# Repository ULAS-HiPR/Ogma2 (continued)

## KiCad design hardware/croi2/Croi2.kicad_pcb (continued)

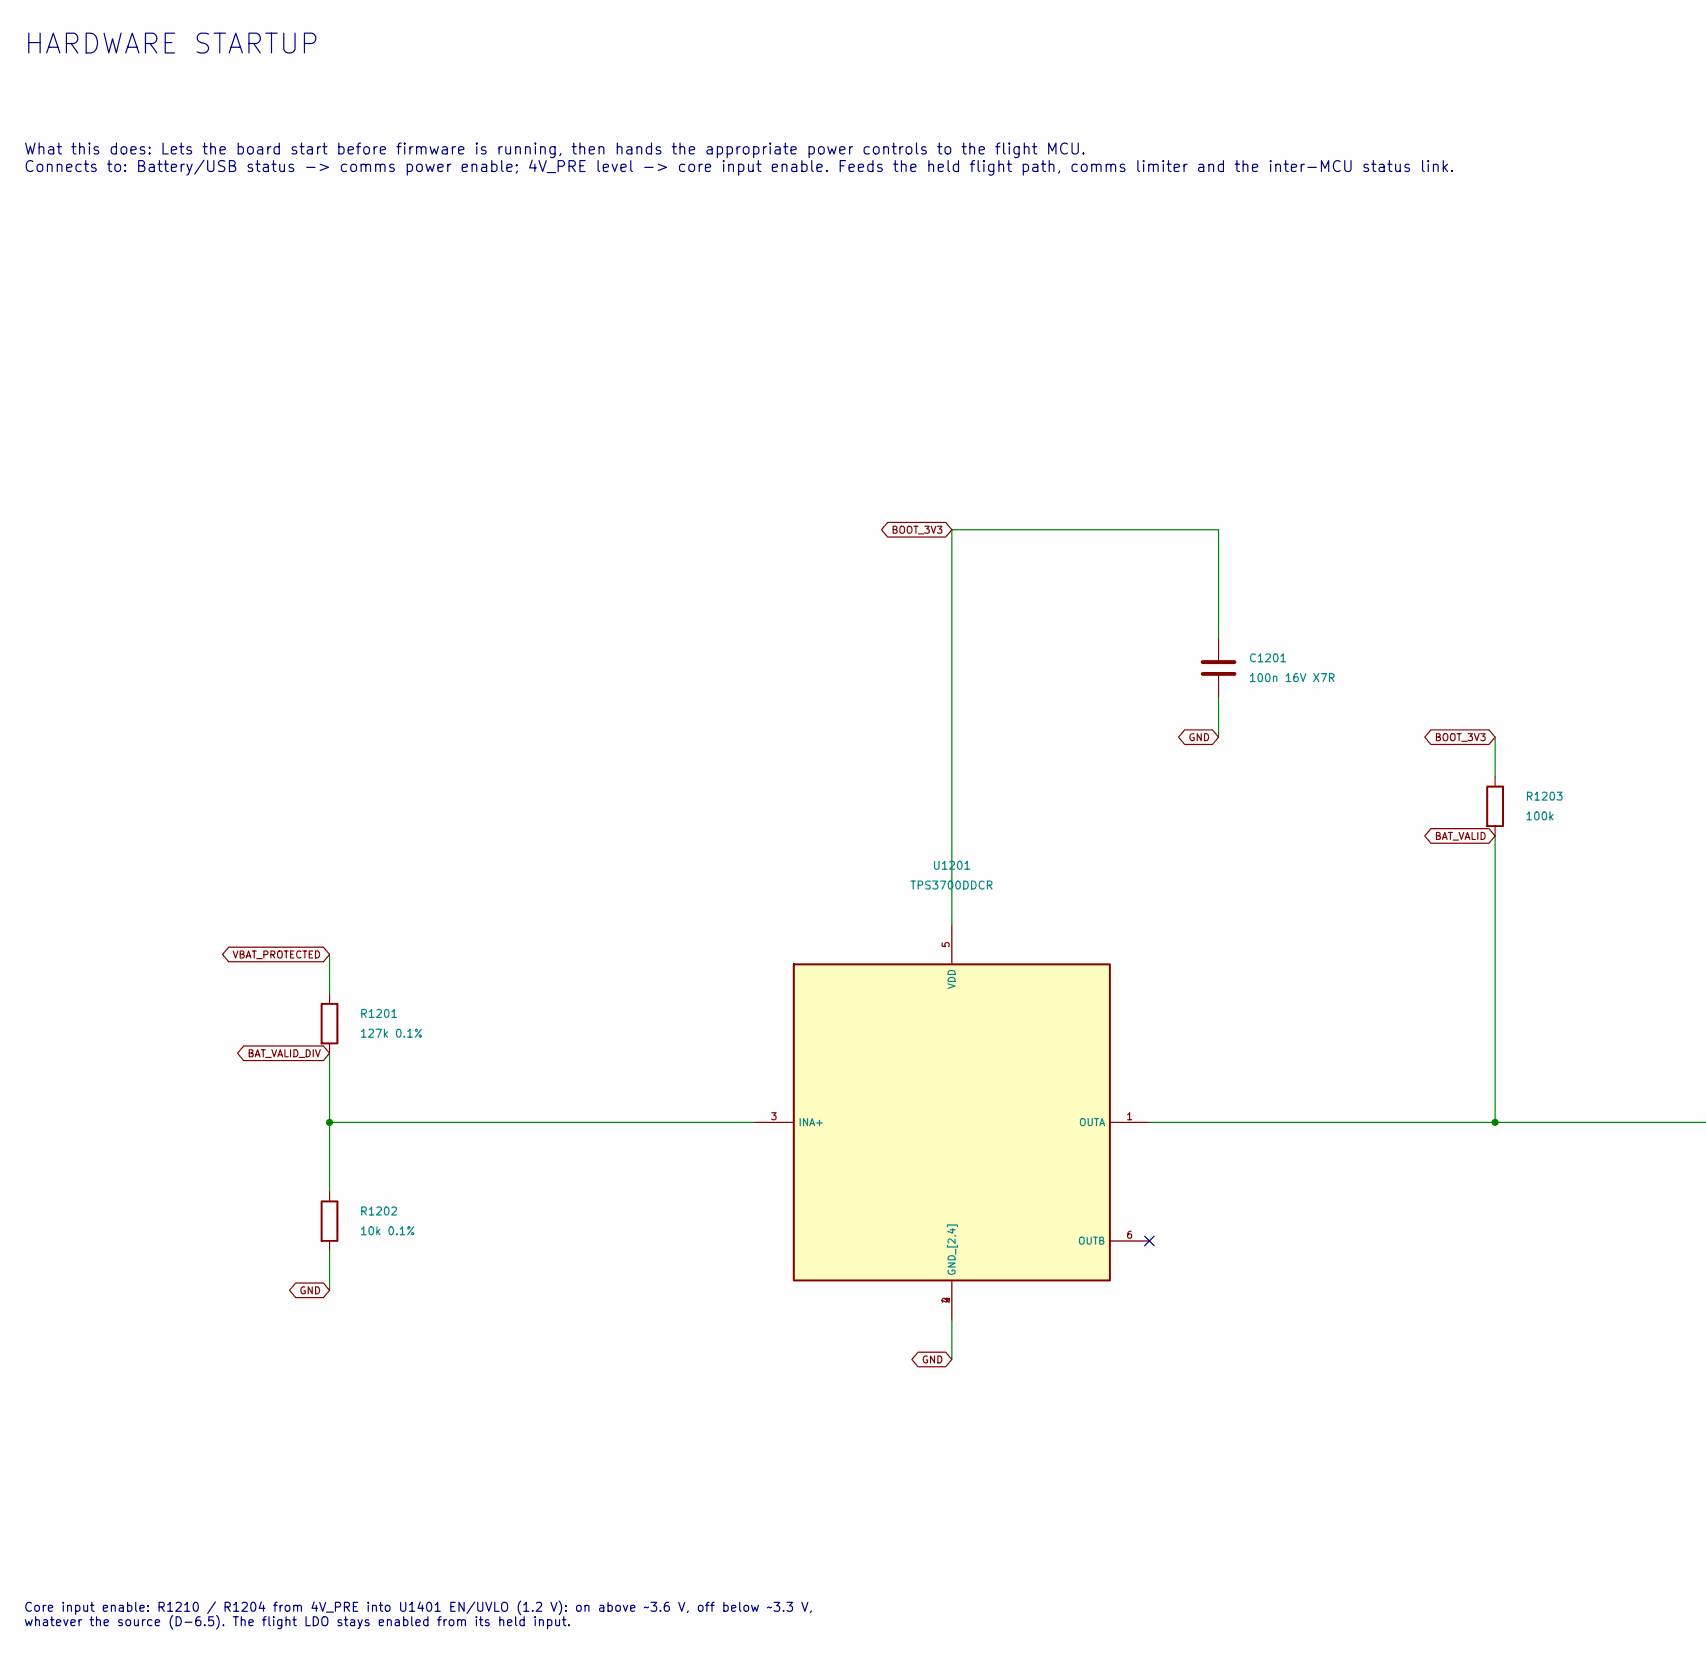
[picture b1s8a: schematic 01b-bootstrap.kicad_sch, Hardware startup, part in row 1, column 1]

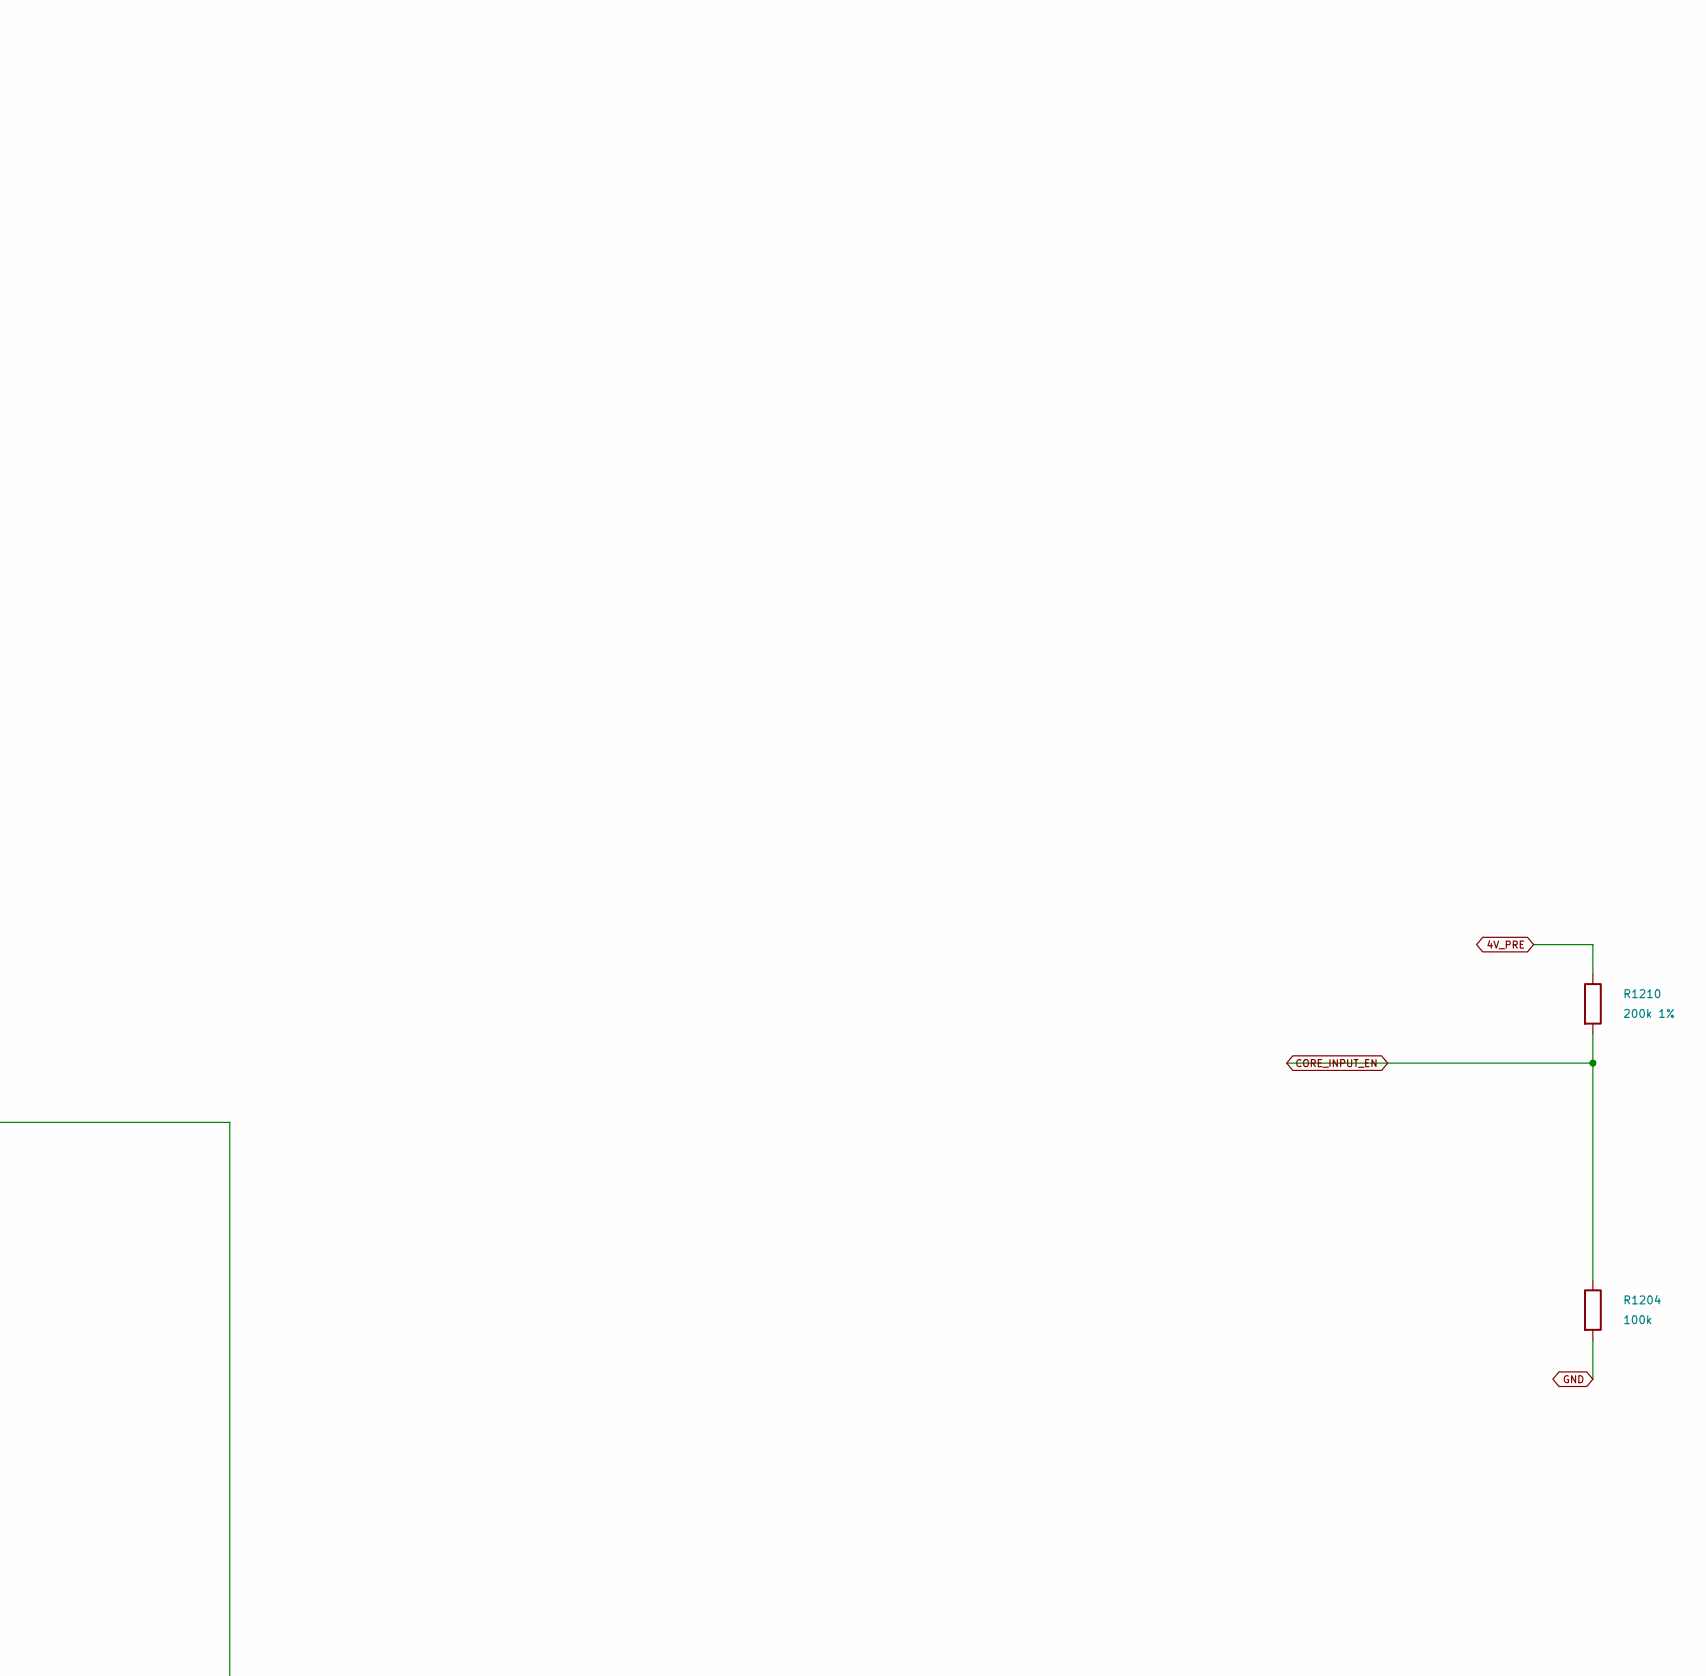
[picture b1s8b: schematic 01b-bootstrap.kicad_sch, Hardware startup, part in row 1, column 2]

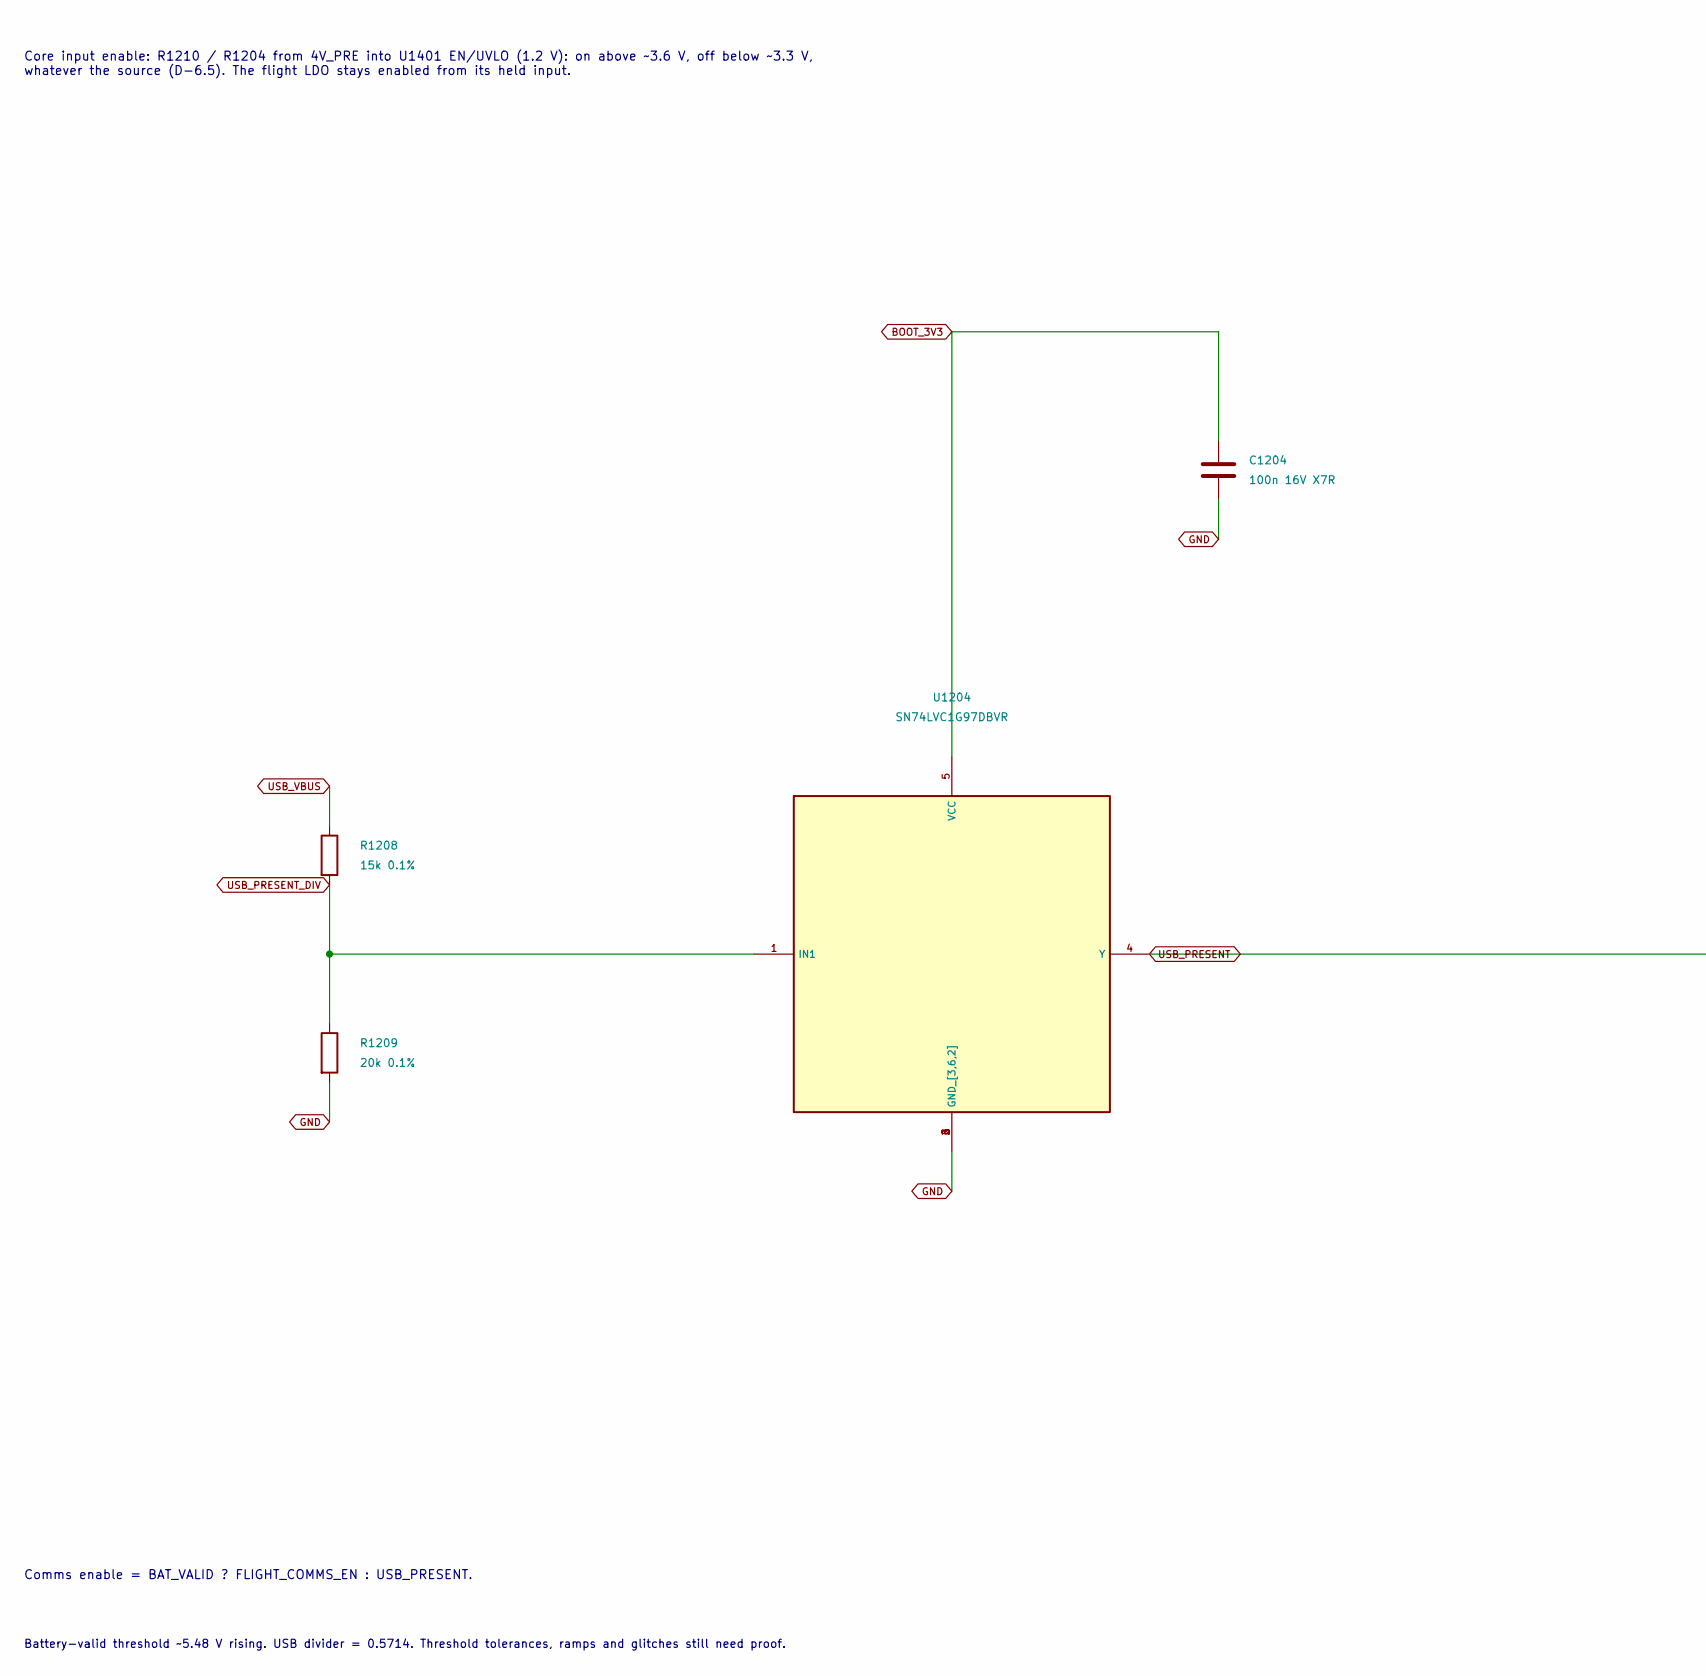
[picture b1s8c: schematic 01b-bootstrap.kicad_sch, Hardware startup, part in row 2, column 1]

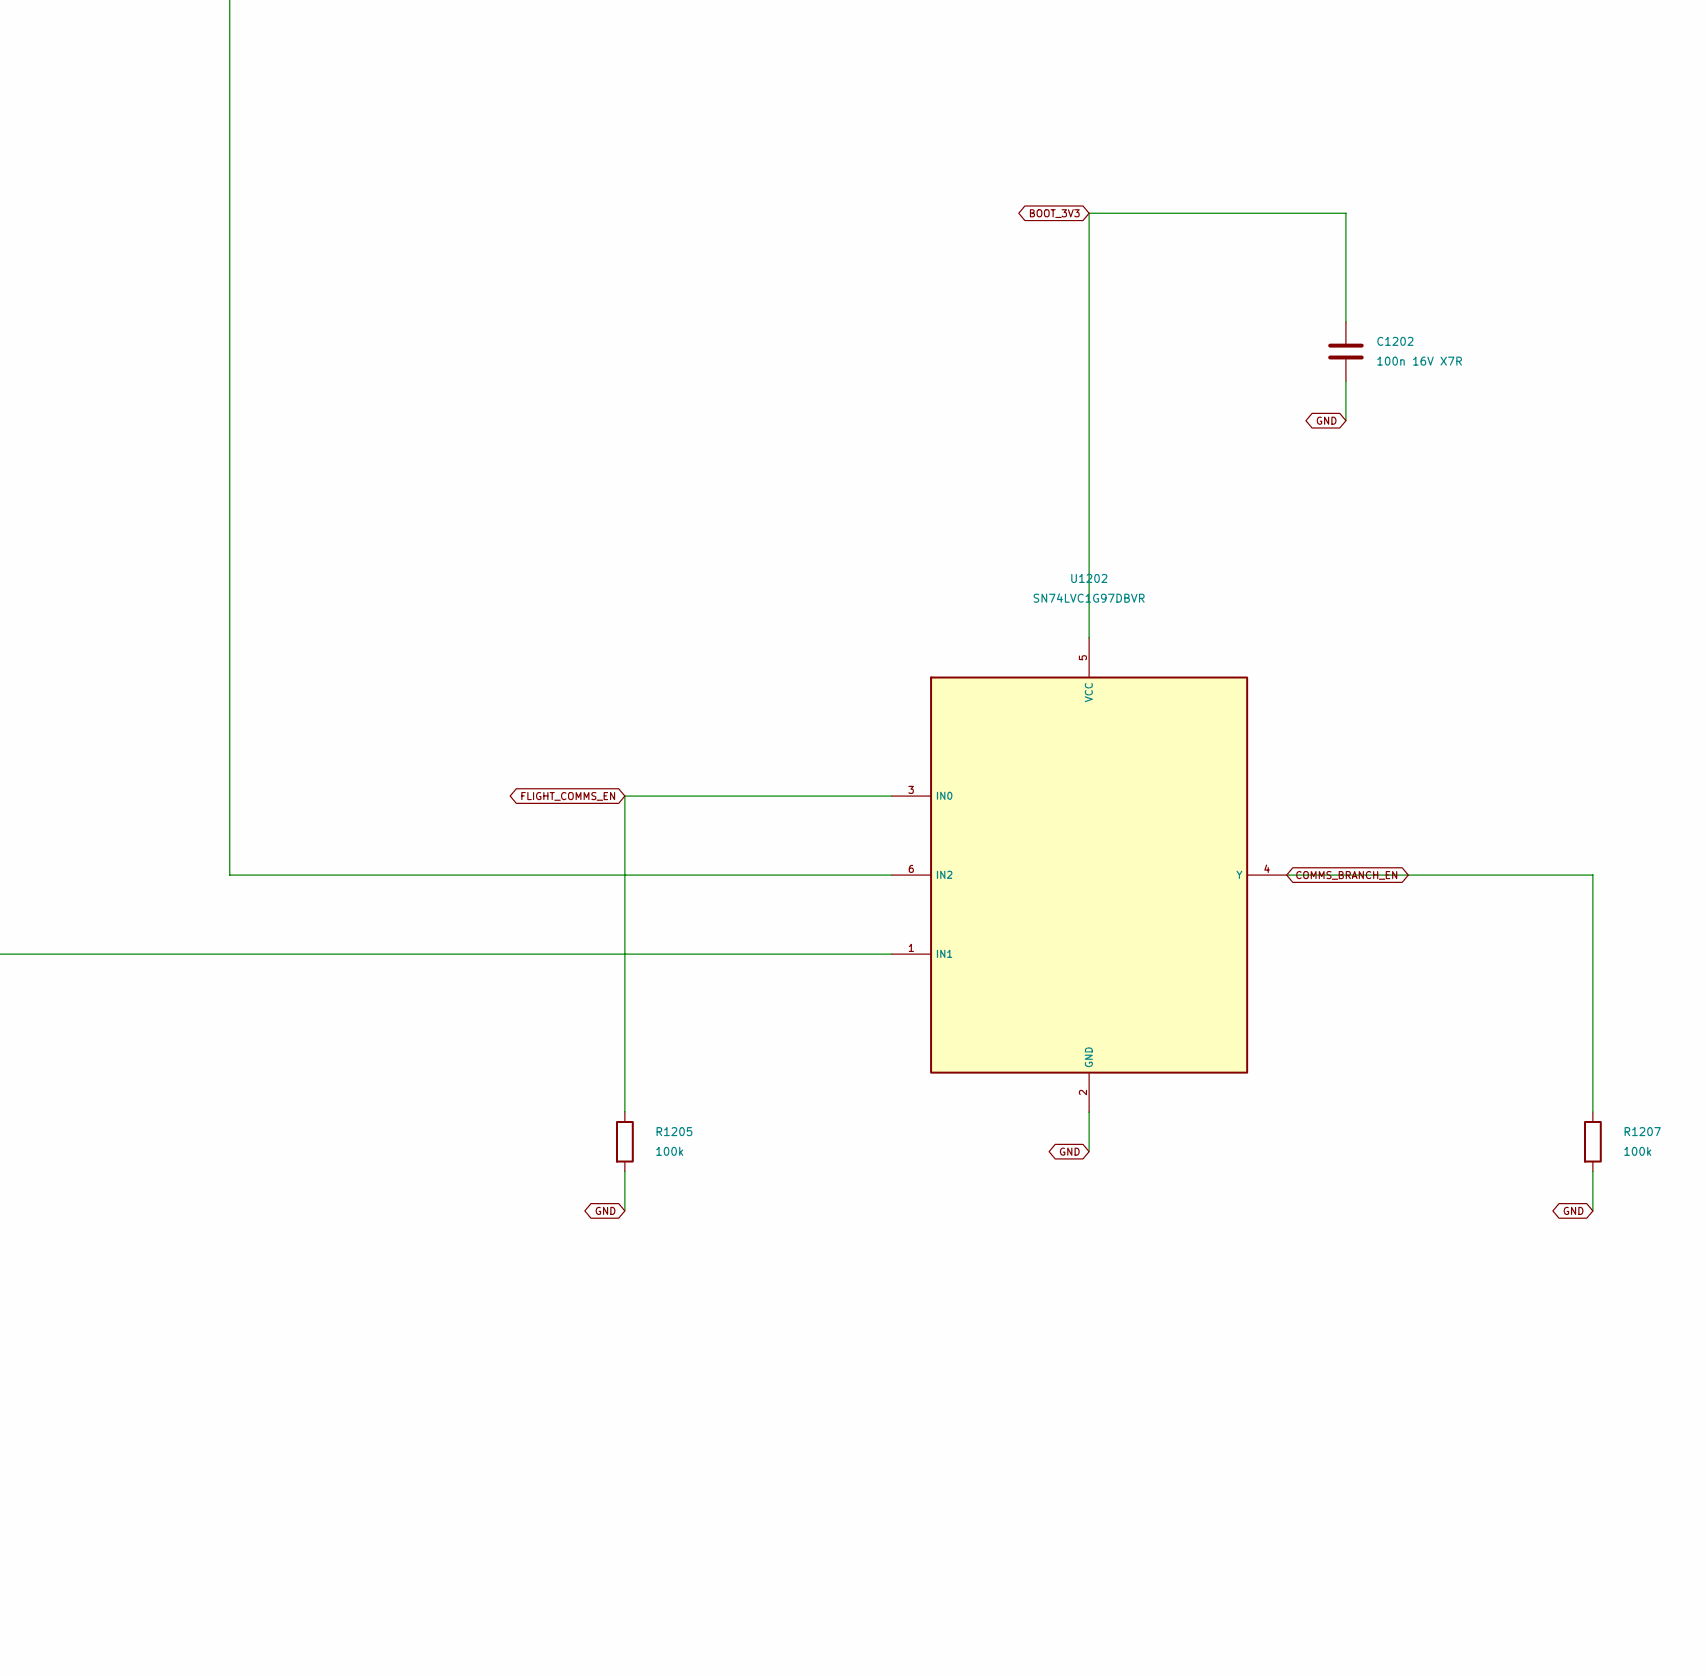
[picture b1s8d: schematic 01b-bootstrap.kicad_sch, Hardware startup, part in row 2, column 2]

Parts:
C1201, C1202, C1204: 100n 16V X7R; C_0402_1005Metric; MPN CL05B104KB54PNC; LCSC C307331
R1201: 127k 0.1%; R_0603_1608Metric
R1202: 10k 0.1%; R_0603_1608Metric
R1203, R1204, R1205, R1207: 100k; R_0402_1005Metric; MPN 0402WGF1003TCE; LCSC C25741
R1208: 15k 0.1%; R_0603_1608Metric
R1209: 20k 0.1%; R_0603_1608Metric
R1210: 200k 1%; R_0402_1005Metric; MPN 0402WGF2003TCE; LCSC C25764
U1201: TPS3700DDCR; MPN TPS3700DDCR
U1202, U1204: SN74LVC1G97DBVR; MPN SN74LVC1G97DBVR

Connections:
4V_PRE: R1210.1; also elsewhere on the board
BAT_VALID: R1203.2, U1201.1 (OUTA), U1202.6 (IN2); also elsewhere on the board
BAT_VALID_DIV: R1201.2, R1202.1, U1201.3 (INA+)
BOOT_3V3: C1201.1, C1202.1, C1204.1, R1203.1, U1201.5 (VDD), U1202.5 (VCC), U1204.5 (VCC); also elsewhere on the board
COMMS_BRANCH_EN: R1207.1, U1202.4 (Y); also elsewhere on the board
CORE_INPUT_EN: R1204.1, R1210.2; also elsewhere on the board
FLIGHT_COMMS_EN: R1205.1, U1202.3 (IN0); also elsewhere on the board
GND: C1201.2, C1202.2, C1204.2, R1202.2, R1204.2, R1205.2, R1207.2, R1209.2, U1201.2 (GND_[2,4]), U1201.4, U1202.2 (GND), U1204.2, U1204.3 (GND_[3,6,2]), U1204.6; also elsewhere on the board
USB_PRESENT: U1202.1 (IN1), U1204.4 (Y); also elsewhere on the board
USB_PRESENT_DIV: R1208.2, R1209.1, U1204.1 (IN1)
USB_VBUS: R1208.1; also elsewhere on the board
VBAT_PROTECTED: R1201.1; also elsewhere on the board

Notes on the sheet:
Core input enable: R1210 / R1204 from 4V_PRE into U1401 EN/UVLO (1.2 V): on above ~3.6 V, off below ~3.3 V, whatever the source (D-6.5). The flight LDO stays enabled from its held input.
Comms enable = BAT_VALID ? FLIGHT_COMMS_EN : USB_PRESENT.
Battery-valid threshold ~5.48 V rising. USB divider = 0.5714. Threshold tolerances, ramps and glitches still need proof.
HARDWARE STARTUP
What this does: Lets the board start before firmware is running, then hands the appropriate power controls to the flight MCU. Connects to: Battery/USB status -> comms power enable; 4V_PRE level -> core input enable. Feeds the held flight path, comms limiter and the inter-MCU status link.

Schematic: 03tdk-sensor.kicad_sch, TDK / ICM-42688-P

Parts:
C3202: 1u 16V X7R; C_0603_1608Metric
C3207: 100n 16V X7R; C_0402_1005Metric; MPN CL05B104KB54PNC; LCSC C307331
C3208: 2.2u 16V X7R; C_0603_1608Metric
C3209: 10n 16V X7R; C_0402_1005Metric; MPN CL05B103KB5NNNC; LCSC C15195
R3201: 47R 1%; R_0402_1005Metric; MPN RC0402FR-0747RL; LCSC C137973
R3205: 47k; R_0402_1005Metric; MPN 0402WGF4702TCE; LCSC C25792
R3207, R3208: 22R; R_0402_1005Metric; MPN 0402WGF220JTCE; LCSC C25092
U3204: ICM-42688-P; MPN ICM-42688-P

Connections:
FLIGHT_3V3: R3201.1, R3205.1; also elsewhere on the board
GND: C3202.2, C3207.2, C3208.2, C3209.2, U3204.6 (GND_[6,7]), U3204.7; also elsewhere on the board
TDK_3V3: C3202.1, C3207.1, C3208.1, C3209.1, R3201.2, U3204.5 (SUPPLY_[5,8]), U3204.8
TDK_DRDY: U3204.4 (INT1_INT); also elsewhere on the board
TDK_MISO: U3204.1 (AP_SDO_AD0); also elsewhere on the board
TDK_MOSI: R3208.1; also elsewhere on the board
TDK_MOSI_DAMP: R3208.2, U3204.14 (AP_SDA_SDIO_SDI)
TDK_NCS: R3205.2, U3204.12 (AP_CS); also elsewhere on the board
TDK_SCK: R3207.1; also elsewhere on the board
TDK_SCK_DAMP: R3207.2, U3204.13 (AP_SCL_SCLK)

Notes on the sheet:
2 FLIGHT-TO-SENSOR SPI
No switches or isolators (D-6.6). Firmware parks a dead sensor's bus pins so the MCU cannot back-power it through the 22 ohm damping (D-2Nov.3). Pull-ups go to FLIGHT_3V3.
1 SUPPLY LINK
What this does: Measures low-g acceleration and rotation with a second IMU from TDK. Connects to: Flight MCU SPI/control/interrupt pins -> this sensor. Fed from FLIGHT_3V3 through R3201, a 47 ohm link, like the ST IMU (D-6.6, D-2Nov.3).
TDK / ICM-42688-P

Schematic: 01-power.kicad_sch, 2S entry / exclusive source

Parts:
C1001: 22n 25V X7R; C_0603_1608Metric
C1002, C1003, C1004: 100n 50V X7R; C_0603_1608Metric
C1005: 10u 16V X7R; C_1206_3216Metric
C1007: 470u 6.3V Al; CP_Elec_6.3x7.7; MPN EEEFKJ471XSP
D1003, D1004: BAT54T1G; D_SOD-123; MPN BAT54T1G
J101: 1053111102; 105311-1102; MPN 1053111102
J102: BM06B-GHS-TBT; JST_GH_BM06B-GHS-TBT_1x06-1MP_P1.25mm_Vertical; MPN BM06B-GHS-TBT(LF)(SN)
Q101: CSD18540Q5B; MPN CSD18540Q5B
Q102: 2N7002; SOT-23
R1001: 100k 0.1%; R_0603_1608Metric
R1002: 22.1k 0.1%; R_0603_1608Metric
R1003: 64.9k 0.1%; R_0603_1608Metric
R1004, R1008: 10k 0.1%; R_0603_1608Metric
R1005: 3k 1%; R_0603_1608Metric
R1006: 22.1k 1%; R_0402_1005Metric; MPN RC0402FR-0722K1L; LCSC C163478
R1007: 39.2k 0.1%; R_0603_1608Metric
R1009: 10k; R_0603_1608Metric
R1010: 100k; R_0402_1005Metric; MPN 0402WGF1003TCE; LCSC C25741
R1011: 0R; R_0603_1608Metric
R1014: 330R; R_0603_1608Metric
R1015: 1M; R_0402_1005Metric; MPN 0402WGF1004TCE; LCSC C26083
TP41: BAT_SOURCE_PG; TestPoint_Pad_D1.0mm
TP42: VBAT_BURRITO_INPUT; TestPoint_Keystone_5190TR_ColorKeyed; MPN 5194TR; LCSC C22388408
TP43: BAT_BLOCK_GATE; TestPoint_Pad_D1.0mm
TP46: VBAT_PROTECTED; TestPoint_Keystone_5190TR_ColorKeyed; MPN 5194TR; LCSC C22388408
U101: TPS26630RGER; MPN TPS26630RGER

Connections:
/01-power/POWER_HOLD_RC: C1007.1, D1003.2 (A), D1004.2 (A), R1014.2
BAT_BLOCK_DRV: Q102.1 (G), U101.4 (DRV)
BAT_BLOCK_GATE: Q101.4 (G), Q102.3 (D), TP43.1 (1_1), U101.3 (B_GATE)
BAT_ILIM: R1005.1, U101.10 (ILIM)
BAT_IMON: R1009.1, U101.13 (IMON)
BAT_OV_DIV: R1003.2, R1004.1, U101.7 (OVP)
BAT_PG_DIV: R1007.2, R1008.1, U101.15 (PGTH)
BAT_SHDN_N: D1003.1 (K), R1006.1, U101.12 (~SHDN); also elsewhere on the board
BAT_SLEW: C1001.1, U101.9 (dVdT)
BAT_SOURCE_FAULT_N: R1011.1, U101.14 (~FLT); also elsewhere on the board
BAT_SOURCE_PG: R1010.2, TP41.1 (1_1), U101.16 (PGOOD)
BAT_UV_DIV: R1001.2, R1002.1, U101.6 (UVLO)
BOOT_3V3: R1010.1; also elsewhere on the board
BRANCH_FAULT_N: R1011.2; also elsewhere on the board
ENERGY_TAP: C1004.1, C1005.1, Q101.5 (D), U101.1 (IN_[1,2]), U101.2; also elsewhere on the board
EXT_3V3: J102.1; also elsewhere on the board
EXT_IO1: D1004.1 (K), J102.5
EXT_IO2: J102.6; also elsewhere on the board
EXT_SCL: J102.2; also elsewhere on the board
EXT_SDA: J102.3; also elsewhere on the board
FC_POWER_HOLD: R1014.1, R1015.1; also elsewhere on the board
GND: C1001.2, C1002.2, C1003.2, C1004.2, C1005.2, C1007.2, J101.2, J102.4, R1002.2, R1004.2, R1005.2, R1006.2, R1008.2, R1009.2, R1015.2, U101.8, U101.11 (MODE), U101.25 (GND_[25,8]); also elsewhere on the board
VBAT_BURRITO_INPUT: C1002.1, J101.1, Q101.1 (SUPPLY_[1,2,3]), Q101.2, Q101.3, Q102.2 (S), R1001.1, R1003.1, TP42.1 (1_1), U101.5 (IN_SYS); also elsewhere on the board
VBAT_PROTECTED: C1003.1, R1007.1, TP46.1 (1_1); also elsewhere on the board
VBAT_SHUNT_IN: U101.17 (SUPPLY_[17,18]), U101.18; also elsewhere on the board

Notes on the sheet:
UV / OV THRESHOLDS AND ENABLE DEFAULT
SOURCE ENTRY -> REVERSE BLOCKING -> ENERGY_TAP -> AUTO-RETRY EFUSE -> SHUNT ON BATTERY MONITOR SHEET
2S ENTRY / EXCLUSIVE SOURCE
ENABLE HOLD / FC_POWER_HOLD
Nano-Fit exact land pattern remains open. Samtec grounds are direct ground bonds. Only one battery source may be physically connected.
22.1k SHDN_N pull-down defaults the battery path OFF. The external master-enable circuit drives BAT_SHDN_N; it is not energetic isolation.
What this does: Accepts one 2S battery source, blocks reverse connection, shuts down a faulty input and retries, and holds the battery enable on through a flight-computer reset aloft (FC_POWER_HOLD). Connects to: Standalone battery or Churro mate -> battery monitor shunt -> logic and output branche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
COPLANAR CHURRO MATE / STANDALONE SOURCE EXCLUSION
Firmware drives PE5 high after launch detect; R1014 charges C1007 in about 0.5 s. If PE5 lets go (a reset aloft), C1007 keeps BAT_SHDN_N and, through J102.8, Churro's AV_SHDN_N above 2 V for >=0.75 s at the worst corner, against the ~0.6 s a restart and re-assert take (D-2Nov.4, D-2Nov.18). R1015 k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

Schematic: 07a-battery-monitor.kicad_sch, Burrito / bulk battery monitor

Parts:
C7101: 10n 100V C0G; C_0603_1608Metric
C7102: 10n 100V X7R; C_0603_1608Metric
C7103: 100n 16V X7R; C_0402_1005Metric; MPN CL05B104KB54PNC; LCSC C307331
R7101: 5m 1% 3W WSLP2512R0050FEA; R_2512_6332Metric
R7102, R7103: 10R; R_0603_1608Metric
R7104: 100R; R_0603_1608Metric
R7105: 0R; R_0603_1608Metric
U7101: INA228AIDGSR; MPN INA228AIDGSR

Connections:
BURRITO_IN_MINUS: C7101.2, R7103.2, U7101.9 (Vin-)
BURRITO_IN_PLUS: C7101.1, R7102.2, U7101.10 (Vin+)
BURRITO_MON_3V3: C7103.1, R7105.2, U7101.6 (VS)
BURRITO_VBUS_FILTER: C7102.1, R7104.2, U7101.8 (Vbus)
ENERGY_TAP: R7104.1; also elsewhere on the board
EXT_3V3: R7105.1; also elsewhere on the board
EXT_SCL: U7101.5 (SCL); also elsewhere on the board
EXT_SDA: U7101.4 (SDA); also elsewhere on the board
GND: C7102.2, C7103.2, U7101.1 (A1), U7101.2 (A0), U7101.7 (GND); also elsewhere on the board
VBAT_PROTECTED: R7101.2, R7103.1; also elsewhere on the board
VBAT_SHUNT_IN: R7101.1, R7102.1; also elsewhere on the board

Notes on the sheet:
Kelvin sense lines leave the shunt pads independently of the load-current copper. Equal 10-ohm input filters; differential 10 nF.
VBUS measures ENERGY_TAP, upstream of the eFuse and the load shunt. Current measures all downstream battery loads, not USB-only consumption.
Current records electrical response. It does not prove that an initiator fired.
What this does: Measures bulk battery current and input voltage, including when Burrito runs without Churro. Connects to: 01-power eFuse -> 5 mOhm shunt -> downstream loads. INA228 reports over the controlled I2C bus on 07. USB-only current does not pass through this shunt.
COMMON BATTERY CURRENT / INPUT VOLTAGE
INA228 address 0x40. A1/A0 low; ALERT unused. Optional I2C failure must not block flight.

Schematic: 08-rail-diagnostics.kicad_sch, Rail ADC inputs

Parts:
C8001, C8003: 10n 16V X7R; C_0603_1608Metric
C8002: 10n 16V X7R; C_0402_1005Metric; MPN CL05B103KB5NNNC; LCSC C15195
C8005: 100n 16V X7R; C_0402_1005Metric; MPN CL05B104KB54PNC; LCSC C307331
R8001, R8002, R8004, R8005, R8007, R8008: 22.1k 0.1%; R_0603_1608Metric
R8003, R8006, R8009: 10k 0.1%; R_0603_1608Metric
U8001: TMUX1511PWR; MPN TMUX1511PWR

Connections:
ADC_FLIGHT_3V3: U8001.6 (D2); also elsewhere on the board
ADC_PYRO_RAIL: U8001.8 (D3); also elsewhere on the board
ADC_VEHICLE_VBAT: U8001.3 (D1); also elsewhere on the board
FLIGHT_3V3: C8005.1, R8004.1, U8001.1 (SEL1), U8001.4 (SEL2), U8001.10 (SEL3), U8001.13 (SEL4), U8001.14 (VDD); also elsewhere on the board
FLIGHT_3V3_MID: R8004.2, R8005.1
FLIGHT_3V3_SCALED: C8002.1, R8005.2, R8006.1, U8001.5 (S2)
GND: C8001.2, C8002.2, C8003.2, C8005.2, R8003.2, R8006.2, R8009.2, U8001.7 (GND); also elsewhere on the board
PYRO_RAIL_MID: R8007.2, R8008.1
PYRO_RAIL_SCALED: C8003.1, R8008.2, R8009.1, U8001.9 (S3)
RECOVERY_ARMED_VBAT: R8007.1; also elsewhere on the board
VBAT_PROTECTED: R8001.1; also elsewhere on the board
VEHICLE_VBAT_MID: R8001.2, R8002.1
VEHICLE_VBAT_SCALED: C8001.1, R8002.2, R8003.1, U8001.2 (S1)

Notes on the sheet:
What this does: Lets the flight MCU read battery, flight-supply and recovery-arm voltages. Connects to: Three rails -> resistor dividers -> power-off signal switches -> flight ADC. Voltage readings are useful evidence, not permission to fire or proof of isolation.
All four analog switches enable only with FLIGHT_3V3; the fourth (pins 11 / 12) is unused since the servos went (D-19Nov.2). Verify injection, leakage, settling and ADC calibration on the first PCBA.
RAIL VOLTAGE DIVIDERS / UNPOWERED ADC BOUNDARY
Recovery-arm voltage is an evidence input. A low reading is not a physical isolation proof.
Each ratio: 10k / (22.1k + 22.1k + 10k). Two top resistors preserve limiting resistance if one shorts.

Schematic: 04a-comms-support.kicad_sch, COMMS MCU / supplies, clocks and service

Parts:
C401, C402, C403, C404, C407, C412, C414: 100n 16V X7R; C_0402_1005Metric; MPN CL05B104KB54PNC; LCSC C307331
C406: 4.7u 16V X7R; C_0603_1608Metric
C409, C410: 2.2u 10V X7R; C_0603_1608Metric
C411, C413: 1u 16V X7R; C_0603_1608Metric
C415, C416: 15p C0G provisional; C_0402_1005Metric; MPN 0402CG150J500NT; LCSC C1548
R401: 0R; R_0603_1608Metric
Y401: ECS-160-10-36Q-ES-TR; MPN ECS-160-10-36Q-ES-TR

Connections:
COMMS_3V3: C401.1, C402.1, C403.1, C404.1, C406.1, C407.1, R401.1; also elsewhere on the board
COMMS_HSE_IN: C415.1, Y401.1 (XTAL); also elsewhere on the board
COMMS_HSE_OUT: C416.1, Y401.3 (XTAL); also elsewhere on the board
COMMS_VCAP: C409.1, C410.1; also elsewhere on the board
COMMS_VDDA: C411.1, C412.1, C413.1, C414.1, R401.2; also elsewhere on the board
GND: C401.2, C402.2, C403.2, C404.2, C406.2, C407.2, C409.2, C410.2, C411.2, C412.2, C413.2, C414.2, C415.2, C416.2, Y401.2 (CASE_GND), Y401.4 (CASE_GND); also elsewhere on the board

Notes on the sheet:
What this does: Gives the comms MCU stable local supplies and its main clock. Connects to: COMMS_3V3 -> U401 on 04-comms-gnss-radio. The 16 MHz crystal belongs only to this MCU; flight has its own clocks.
Digital bypass, VCAP and VDDA remain different electrical domains. Crystal load capacitances are provisional, not measured startup margins.
COMMS_VCAP / LOCAL BYPASS
COMMS_3V3 / LOCAL BYPASS
Y401 / ECS-160-10-36Q-ES-TR
COMMS MCU / SUPPLIES, CLOCKS AND SERVICE
COMMS_VDDA / LOCAL BYPASS

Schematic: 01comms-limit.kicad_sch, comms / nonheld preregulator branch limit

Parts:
C1501: 100n 16V X7R; C_0402_1005Metric; MPN CL05B104KB54PNC; LCSC C307331
C1502: 1u 16V X7R; C_0603_1608Metric
R1501: 0R; R_0603_1608Metric
R1502: 100k; R_0402_1005Metric; MPN 0402WGF1003TCE; LCSC C25741
R1503: 10k; R_0402_1005Metric; MPN 0402WGF1002TCE; LCSC C25744
R1504: 66.5k 1%; R_0603_1608Metric
U1501: TPS2553DBVR-1; MPN TPS2553DBVR-1

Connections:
4V_PRE: C1501.1, U1501.1 (IN); also elsewhere on the board
BRANCH_FAULT_N: U1501.4 (~FAULT); also elsewhere on the board
COMMS_BRANCH_EN: R1502.1, U1501.3 (EN); also elsewhere on the board
COMMS_LDO_IN: C1502.1, R1501.2, R1503.1; also elsewhere on the board
COMMS_LDO_IN_ILIM: R1504.1, U1501.5 (ILIM)
COMMS_LDO_IN_PRELINK: R1501.1, U1501.6 (OUT)
GND: C1501.2, C1502.2, R1502.2, R1503.2, R1504.2, U1501.2 (GND); also elsewhere on the board

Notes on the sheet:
Removable output link follows the latch-off switch. Local input/output bypass, enable pull-down and output bleed shown explicitly.
COMMS / NONHELD PREREGULATOR BRANCH LIMIT
What this does: Limits current into the comms branch so a fault there is less able to collapse the shared supply. Connects to: 01c 4 V supply and 01b comms permission -> 01comms-ldo. It latches off after a qualifying fault; restart behaviour needs testing.
Current limit set by R1504 66.5k: 351-449 mA calculated. Native connectivity is preserved; no first-PCBA fault test has been performed.

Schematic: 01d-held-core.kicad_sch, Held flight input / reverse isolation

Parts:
C1401: 100n 16V X7R; C_0402_1005Metric; MPN CL05B104KB54PNC; LCSC C307331
C1402: 47n 16V X7R; C_0402_1005Metric; MPN TCC0402X7R473K500AT; LCSC C880605
C1403: 1000u 6.3V polymer; CP_Elec_8x10; MPN PCW0J102MCO1GS
R1401: 26.7k 0.1%; R_0603_1608Metric
R1402, R1404: 10k 0.1%; R_0603_1608Metric
R1403: 20k 0.1%; R_0603_1608Metric
R1405: 100k; R_0402_1005Metric; MPN 0402WGF1003TCE; LCSC C25741
R1406: 10k; R_0603_1608Metric
TP27: CORE_HELD_4V; TestPoint_Keystone_5190TR_ColorKeyed; MPN 5194TR; LCSC C22388408
U1401: LM73100RPWR; MPN LM73100RPWR

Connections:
4V_PRE: C1401.1, R1401.1, U1401.5 (IN); also elsewhere on the board
BOOT_3V3: R1405.1; also elsewhere on the board
CORE_HELD_4V: C1403.1, R1403.1, TP27.1 (1_1), U1401.6 (OUT); also elsewhere on the board
CORE_IMON: R1406.1, U1401.9 (IMON)
CORE_INPUT_EN: U1401.1 (EN_UVLO); also elsewhere on the board
CORE_INPUT_PG: R1405.2, U1401.3 (PG)
CORE_OV_DIV: R1401.2, R1402.1, U1401.2 (OVLO)
CORE_PG_DIV: R1403.2, R1404.1, U1401.4 (PGTH)
CORE_SLEW: C1402.1, U1401.7 (DVDT)
GND: C1401.2, C1402.2, C1403.2, R1402.2, R1404.2, R1406.2, U1401.8 (GND); also elsewhere on the board

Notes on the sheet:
What this does: Reserves local energy for the flight MCU during a brief input dip, and blocks that energy flowing back upstream. Connects to: 01c 4 V supply, enabled by its own level (01b) -> 01flight-ldo. Hold-up time is not proved.
The permission gate is before hold-up. Flight LDO enable follows CORE_HELD_4V and does not fall with upstream CORE_INPUT_EN.
HELD FLIGHT INPUT / REVERSE ISOLATION
C1403: Nichicon PCW0J102MCO1GS, 1000 uF 6.3 V polymer, 8 x 10.5 mm, flight hold-up only. Land pattern to check against Nichicon's drawing; hold-up time not proved.

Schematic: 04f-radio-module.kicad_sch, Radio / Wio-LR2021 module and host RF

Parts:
C4611: 100n 16V X7R; C_0402_1005Metric; MPN CL05B104KB54PNC; LCSC C307331
C4612: 10u 16V X7R; C_1206_3216Metric
C4613: 100u 16V X5R; C_1210_3225Metric; MPN EMK325ABJ107MM-P
D4601: PESD5V0F1BL,315; D_SOD-882; MPN PESD5V0F1BL,315; LCSC C45961
J4601: 132134; SMA_Amphenol_132134_Vertical; MPN 132134
R4614, R4615, R4616, R4617, R4618, R4619, R4620: 470R; R_0402_1005Metric; MPN 0402WGF4700TCE; LCSC C25117
R4621: 10k; R_0402_1005Metric; MPN 0402WGF1002TCE; LCSC C25744
U4606: Wio-LR2021; MPN Wio-LR2021 / SKU 100058045

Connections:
COMMS_3V3: C4611.1, C4612.1, C4613.1, R4621.1, U4606.1 (VCC_IN); also elsewhere on the board
GND: C4611.2, C4612.2, C4613.2, D4601.2 (A2), J4601.2 (Ext), U4606.9 (GND), U4606.11 (GND), U4606.12 (GND), U4606.14 (GND), U4606.15 (GND), U4606.20 (GND); also elsewhere on the board
LORA_BUSY: R4619.1; also elsewhere on the board
LORA_BUSY_MOD: R4619.2, R4621.2, U4606.8 (BUSY)
LORA_DIO1: R4620.1; also elsewhere on the board
LORA_DIO1_MOD: R4620.2, U4606.2 (DIO5)
LORA_MISO: R4616.1; also elsewhere on the board
LORA_MISO_MOD: R4616.2, U4606.4 (MISO)
LORA_MOSI: R4615.1; also elsewhere on the board
LORA_MOSI_MOD: R4615.2, U4606.5 (MOSI)
LORA_NCS: R4617.1; also elsewhere on the board
LORA_NCS_MOD: R4617.2, U4606.7 (NSS)
LORA_RESET_N: R4618.1; also elsewhere on the board
LORA_RESET_N_MOD: R4618.2, U4606.3 (RESET)
LORA_RF_SUBG: D4601.1 (A1), J4601.1 (In), U4606.10 (Sub-G_RF)
LORA_SCK: R4614.1; also elsewhere on the board
LORA_SCK_MOD: R4614.2, U4606.6 (SCK)

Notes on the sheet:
Open-drain BUSY pull-up
470-ohm values are initial damping choices; verify SPI edge/timing margin on the first PCBA.
RADIO MODULE / SIGNAL DAMPING / EXTERNAL ANTENNA
One 50-ohm sub-GHz path to vertical SMA. Do not route a second RF stub to the unused module RF contacts.
All module ground pins connect to the plane. Physical RF return, matching and coexistence remain layout / installed tests.
D4601: ESD on the LoRa port, as D4501 on GNSS (D-22Nov.20). A path for static the antenna collects; 0.4 pF.
What this does: Sends telemetry over the sub-GHz radio link. Connects to: Comms SPI/status signals through 04e -> Wio-LR2021 -> vertical SMA/external antenna. Flight does not wait for radio to succeed.

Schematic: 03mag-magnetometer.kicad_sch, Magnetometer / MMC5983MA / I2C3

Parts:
C3701: 10u 16V X7R; C_1206_3216Metric
C3702: 1u 16V X7R; C_0603_1608Metric
C3703, C3704: 100n 16V X7R; C_0402_1005Metric; MPN CL05B104KB54PNC; LCSC C307331
R3701, R3704, R3705: 22R; R_0402_1005Metric; MPN 0402WGF220JTCE; LCSC C25092
R3702, R3703: 2.7k; R_0402_1005Metric; MPN FRC0402F2701TS; LCSC C2909332
U3701: MMC5983MA; MPN MMC5983MA

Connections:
FLIGHT_3V3: R3701.1, R3702.1, R3703.1; also elsewhere on the board
GND: C3701.2, C3702.2, C3703.2, C3704.2, U3701.9 (GND), U3701.11 (GND); also elsewhere on the board
MAG_3V3: C3701.1, C3702.1, C3703.1, C3704.1, R3701.2, U3701.2 (VDD), U3701.4 (SPI_CS), U3701.10 (CAP), U3701.13 (VDDIO)
MAG_INT: U3701.15 (INT); also elsewhere on the board
MAG_SCL: R3702.2, R3704.1; also elsewhere on the board
MAG_SCL_DAMP: R3704.2, U3701.1 (SCL/SPI_SCK)
MAG_SDA: R3703.2, R3705.1; also elsewhere on the board
MAG_SDA_DAMP: R3705.2, U3701.16 (SDA/SPI_SDI)

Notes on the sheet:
1 SUPPLY LINK
2 SENSOR, I2C3 AND DATA READY
22 ohm link, not 47: VDD's minimum is 2.8 V and the SET/RESET pulses come through the link (D-2Nov.11). C3701 is the SET/RESET reservoir, at CAP (pin 10); C3702 / C3703 at VDD (pin 2); C3704 at VDDIO (pin 13). I2C only: SPI_CS tied to VDDIO; SDO and the NC pads unconnected. Address 0x30. Pull-ups g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
Placement: layout guide C09a. Footprint: KiCad's MEMSIC LGA-16 3 x 3 mm pattern (made from the MMC5883MA drawing); check its pads against the MMC5983MA drawing before layout.
What this does: Measures the magnetic field for heading and roll, read at 100 Hz and logged. Non-essential: it never gates the watchdog or the estimator (D-2Nov.11). Connects to: FLIGHT_3V3 through R3701 -> MAG_3V3; I2C3 (PA8 MAG_SCL, PC9 MAG_SDA) and MAG_INT (PE6) on 02-flight-mcu.
MAGNETOMETER / MMC5983MA / I2C3

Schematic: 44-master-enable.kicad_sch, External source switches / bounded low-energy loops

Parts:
C1006: 100n 16V X7R; C_0603_1608Metric; MPN 100n 16V X7R
D1002: BAS116,215; SOT-23; MPN BAS116,215
J103: 43650-0215; Molex_Micro-Fit_3.0_43650-0215_1x02_P3.00mm_Vertical; MPN 43650-0215; LCSC C293740
R1012, R1013: 4.7k 1% 0.75W; R_2010_5025Metric; MPN CRCW20104K70FKEF
U1002: LM4040CEM3-3.0/NOPB; SOT-23; MPN LM4040CEM3-3.0/NOPB

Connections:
BAT_SHDN_N: C1006.1, J103.2; also elsewhere on the board
BAT_SWITCH_3V: J103.1, R1013.2, U1002.1 (K)
BAT_SW_DIODE: D1002.3 (K), R1012.1
BAT_SW_RMID: R1012.2, R1013.1
GND: C1006.2, U1002.2 (A); also elsewhere on the board
VBAT_BURRITO_INPUT: D1002.1 (A); also elsewhere on the board

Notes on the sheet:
Burrito battery source / J103: 1 = 3 V bias, 2 = SHDN return
EXTERNAL MASTER ENABLE / maintained dry contacts
What this does: Lets an external maintained switch turn Burrito's battery path on and off, without carrying load current through the switch. Connects to: J103 pin 1 is a limited 3 V bias; pin 2 returns to the eFuse SHDN input on 01-power. Open/unplugged means electronic OFF, not physical disconnect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
R1006 on 01-power is the local 22.1k SHDN pull-down. Open contact = electronic OFF. 100nF is an edge filter, not a guaranteed debounce circuit. SHDN cycling clears a latched fault. Foinse-fed use: retain a deliberate closed Burrito enable plug, or add an independent third switch pole. USB may still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
